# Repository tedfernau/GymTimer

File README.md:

A simple timer with a button and a vibration motor. 

I was thinking of this as a way to time intervals during workouts, or for phone-free timing in the sauna.

I designed it for a belt holder, but then I realized I would never let anyone see this in public!

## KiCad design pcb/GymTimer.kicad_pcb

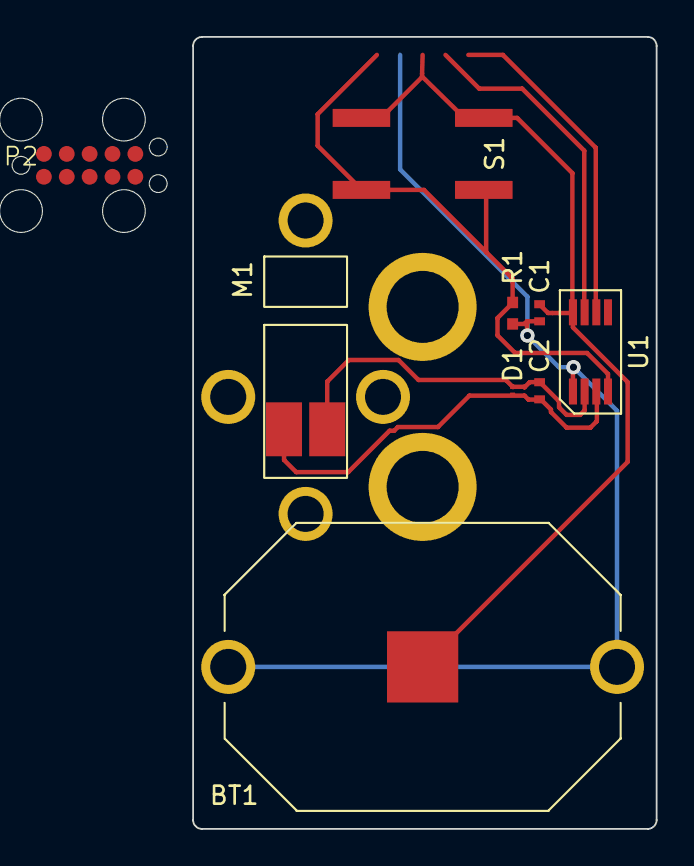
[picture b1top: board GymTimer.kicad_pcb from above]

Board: 2 copper layers, 25.8 x 44.0 mm, 9 parts (0 on the bottom side), 8 nets.

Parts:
BT1: 3; BK-913
C1, C2: .1uF; cap-0402
D1: diode_TVS_bidirectional; TVS - PESD4V0Y1BSFYL
M1: VibrationDCmotor; Z4TH7B2120042P
P2: PICprogrammingheader; TC2050-idc
R1: 10k; res_0402
S1: SPST_NO_4pin; SPST-NO-EVQ-Q2U02W
U1: PIC12F1571; PIC12F1571 MSOP8

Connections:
3V: BT1.1 (+), C1.1, P2.7 (VDD), R1.1, U1.1 (VDD)
GND: BT1.2 (-), C1.2, P2.5 (GND), S1.1 (A), S1.2 (A), U1.8 (VSS)
unnamed: C2.1, D1.2
unnamed: C2.2, D1.1
unnamed: M1.1 (+), U1.2 (RA5)
unnamed: M1.2 (-), U1.3 (RA4)
unnamed: P2.9 (MCLR_N), R1.2, S1.3 (B), S1.4 (B), U1.4 (RA3/MCLR/VPP)
unnamed: P2.3 (PGD), U1.7 (RA0/ICSPDAT)

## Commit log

2025-04-04 add GymTimer files to Github
2025-04-04 add picture
2025-05-22 add built picture
2025-05-22 fixing readme to add built photo
